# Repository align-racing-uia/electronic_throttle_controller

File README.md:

<h1 align="center"> Electronic Throttle Body Controller </h1> <br>
<p align="center">
    
</p>

<!-- START doctoc generate TOC please keep comment here to allow auto update -->
<!-- DON'T EDIT THIS SECTION, INSTEAD RE-RUN doctoc TO UPDATE -->
## Table of contents

- [Introduction](#introduction)
- [Align Racing UiA](#alignracinguia)
- [Rules for file structure](#rulesforfilestructure)
- [License](#license)

<!-- END doctoc generated TOC please keep comment here to allow auto update -->

## Introduction

This is the repository for Align Racing's formula student race car's different systems.

## Align Racing UiA

<a href="http://www.alignracing.no/">Align Racing UiA (AR)</a> is a multidisciplinary student organisation at <a href="https://www.uia.no/">The University of Agder (UiA)</a>, that take part in the world’s largest yearly engineering competition; <a href="https://www.imeche.org/events/formula-student">Formula Student (FS)</a>. The organisation continuously consists of around 60 students, from a wide variety of disciplines. The competition includes developing, building, budgeting and marketing a small scale formula type racing car. AR takes this a bit further by having more focus on developing a strong organisation, open for all disciplines, that gives the members a taste of future work-life.

## Rules

## Contribution

## License
All content included in this Git repository is under the license:

Creative Commons Attribution-NonCommercial-ShareAlike 4.0 International

You are free to:
* <b> Share </b> — copy and redistribute the material in any medium or format
* <b> Adapt </b> — remix, transform, and build upon the material

Under the following terms:
* <b> Attribution </b> — You must give appropriate credit, provide a link to the license, and indicate if changes were made. You may do so in any reasonable manner, but not in any way that suggests the licensor endorses you or your use.
* <b> NonCommercial </b> — You may not use the material for commercial purposes.
* <b> ShareAlike </b> — If you remix, transform, or build upon the material, you must distribute your contributions under the same license as the original.
* <b> No additional restrictions </b> — You may not apply legal terms or technological measures that legally restrict others from doing anything the license permits.

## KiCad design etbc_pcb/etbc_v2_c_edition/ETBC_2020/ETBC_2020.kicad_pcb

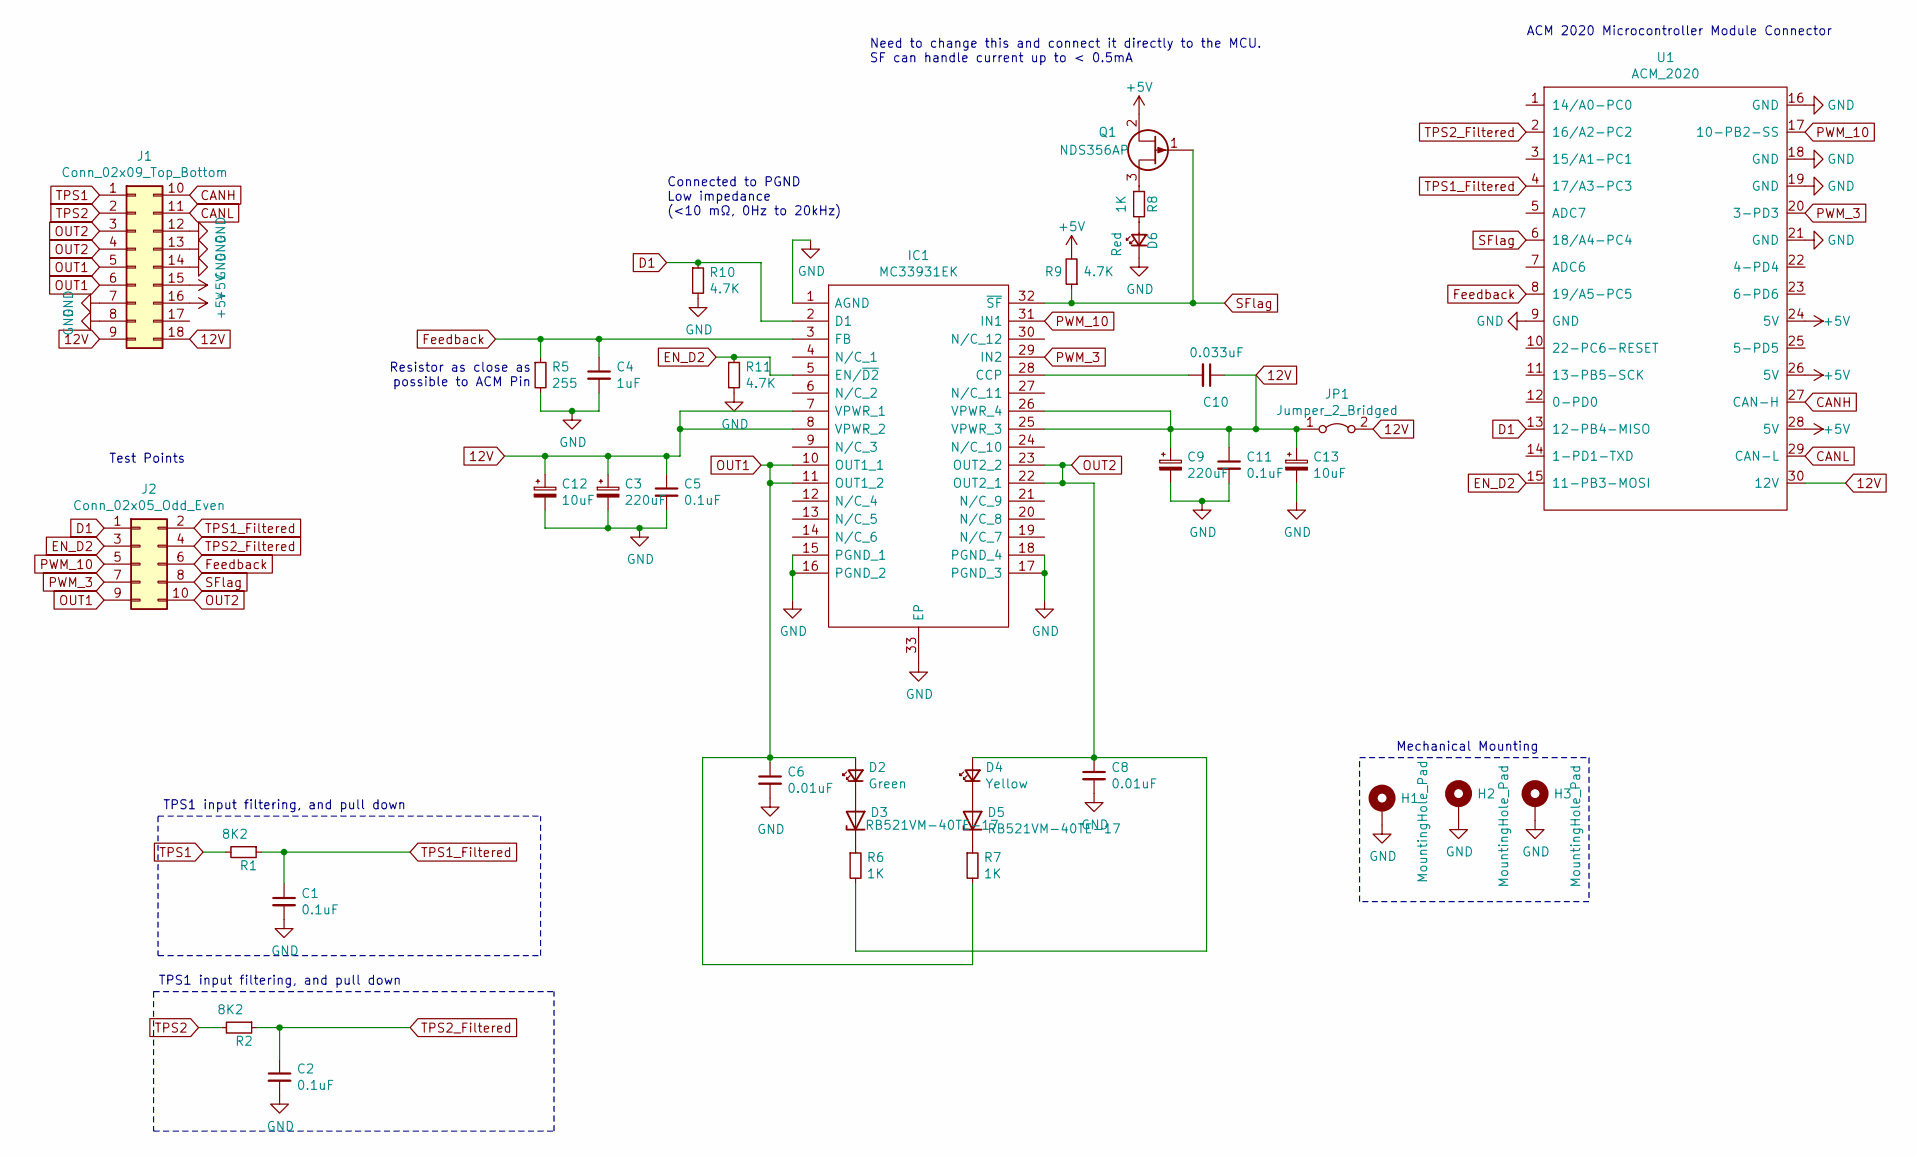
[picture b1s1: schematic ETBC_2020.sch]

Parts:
C1, C2, C5, C11: 0.1uF; C_0603_1608Metric_Pad1.05x0.95mm_HandSolder
C3, C9: 220uF; CP_Elec_6.3x7.7
C4: 1uF; C_0603_1608Metric_Pad1.05x0.95mm_HandSolder
C6, C8: 0.01uF; C_0603_1608Metric_Pad1.05x0.95mm_HandSolder
C10: 0.033uF; C_0603_1608Metric_Pad1.05x0.95mm_HandSolder
C12, C13: 10uF; CP_EIA-3216-10_Kemet-I_Pad1.58x1.35mm_HandSolder
D2: Green; D_1206_3216Metric_Pad1.42x1.75mm_HandSolder
D3, D5: RB521VM-40TE-17; D_SOD-323F
D4: Yellow; D_1206_3216Metric_Pad1.42x1.75mm_HandSolder
D6: Red; D_1206_3216Metric_Pad1.42x1.75mm_HandSolder
H1, H2, H3: MountingHole_Pad; MountingHole_3.2mm_M3_Pad_Via
IC1: MC33931EK; SOP65P1030X245-33N; Manufacturer_Part_Number MC33931EK; Mouser Part Number 841-MC33931EK
J1: Conn_02x09_Top_Bottom; JAE_MX23A18NF1
J2: Conn_02x05_Odd_Even; PinHeader_2x05_P2.54mm_Vertical
JP1: Jumper_2_Bridged; Jumper PWR 25 26
Q1: NDS356AP; SOT-23
R1, R2: 8K2; R_0603_1608Metric_Pad1.05x0.95mm_HandSolder
R5: 255; R_0603_1608Metric_Pad1.05x0.95mm_HandSolder
R6, R7, R8: 1K; R_0603_1608Metric_Pad1.05x0.95mm_HandSolder
R9, R10, R11: 4.7K; R_0603_1608Metric_Pad1.05x0.95mm_HandSolder
U1: ACM_2020; ACM_2020_Footprint_wo_silk

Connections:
12V: C3.1, C5.1, C9.1, C10.1, C11.1, C12.1, C13.1, IC1.7 (VPWR_1), IC1.8 (VPWR_2), IC1.25 (VPWR_3), IC1.26 (VPWR_4), J1.9, J1.18, JP1.1 (A), JP1.2 (B), U1.30 (12V)
+5V: J1.15, J1.16, Q1.2 (S), R9.2, U1.24 (5V), U1.26 (5V), U1.28 (5V)
CANH: J1.10, U1.27 (CAN-H)
CANL: J1.11, U1.29 (CAN-L)
D1: IC1.2 (D1), J2.1, R10.1, U1.13 (12-PB4-MISO)
EN_D2: IC1.5 (EN/~D2), J2.3, R11.1, U1.15 (11-PB3-MOSI)
Feedback: C4.1, IC1.3 (FB), J2.6, R5.1, U1.8 (19/A5-PC5)
GND: C1.2, C2.2, C3.2, C4.2, C5.2, C6.2, C8.2, C9.2, C11.2, C12.2, C13.2, D6.1 (K), H1.1, H2.1, H3.1, IC1.1 (AGND), IC1.15 (PGND_1), IC1.16 (PGND_2), IC1.17 (PGND_3), IC1.18 (PGND_4), IC1.33 (EP), J1.7, J1.8, J1.12, J1.13, J1.14, R5.2, R10.2, R11.2, U1.9 (GND), U1.16 (GND), U1.18 (GND), U1.19 (GND), U1.21 (GND)
unnamed: C10.2, IC1.28 (CCP)
unnamed: D2.1 (K), D3.2 (A)
unnamed: D3.1 (K), R6.1
unnamed: D4.1 (K), D5.2 (A)
unnamed: D5.1 (K), R7.1
unnamed: D6.2 (A), R8.2
unnamed: Q1.3 (D), R8.1
OUT1: C6.1, D2.2 (A), IC1.10 (OUT1_1), IC1.11 (OUT1_2), J1.5, J1.6, J2.9, R7.2
OUT2: C8.1, D4.2 (A), IC1.22 (OUT2_1), IC1.23 (OUT2_2), J1.3, J1.4, J2.10, R6.2
PWM_3: IC1.29 (IN2), J2.7, U1.20 (3-PD3)
PWM_10: IC1.31 (IN1), J2.5, U1.17 (10-PB2-SS)
SFlag: IC1.32 (~SF), J2.8, Q1.1 (G), R9.1, U1.6 (18/A4-PC4)
TPS1: J1.1, R1.2
TPS1_Filtered: C1.1, J2.2, R1.1, U1.4 (17/A3-PC3)
TPS2: J1.2, R2.2
TPS2_Filtered: C2.1, J2.4, R2.1, U1.2 (16/A2-PC2)

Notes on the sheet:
TPS1 input filtering, and pull down
Resistor as close as possible to ACM Pin
Connected to PGND Low impedance (<10 mΩ, 0Hz to 20kHz)
Need to change this and connect it directly to the MCU. SF can handle current up to < 0.5mA
Mechanical Mounting
Test Points
ACM 2020 Microcontroller Module Connector

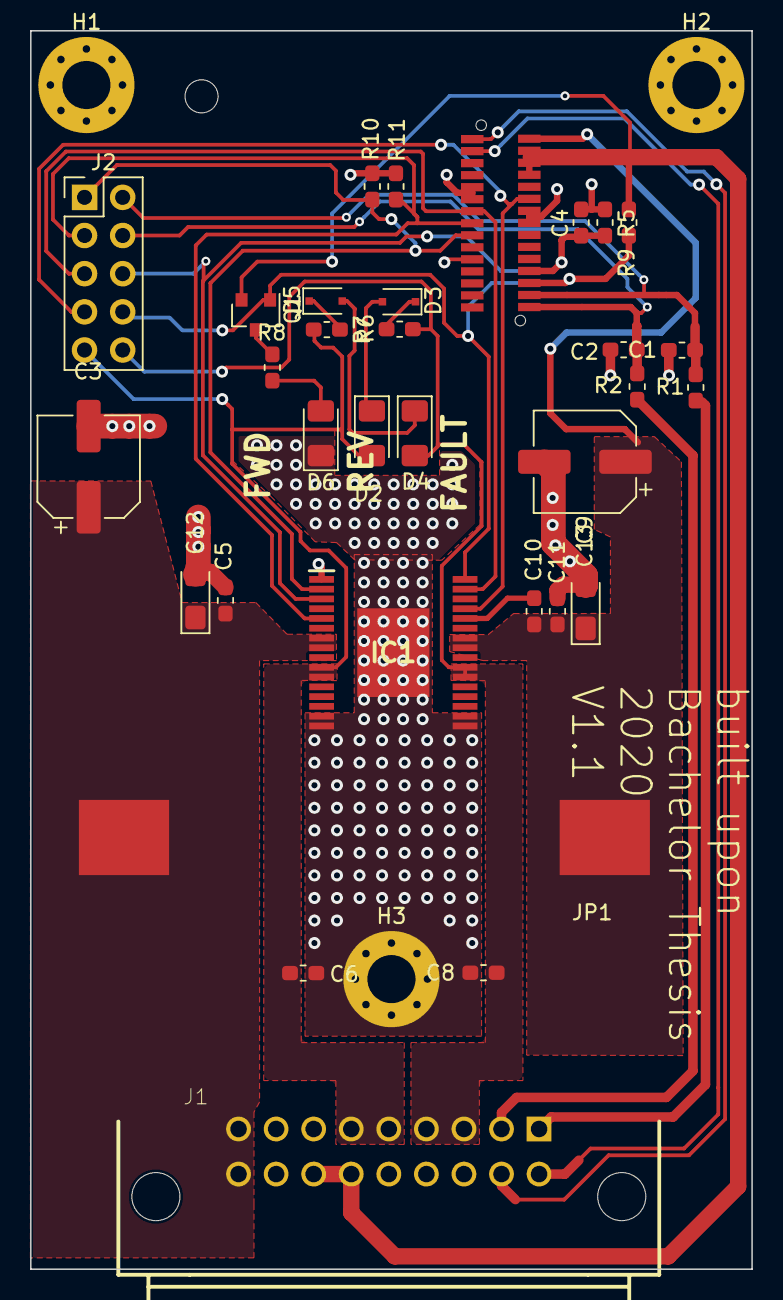
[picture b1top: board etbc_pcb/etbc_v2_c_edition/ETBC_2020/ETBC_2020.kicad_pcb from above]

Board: 2 copper layers, 48.0 x 82.4 mm, 35 parts (0 on the bottom side), 24 nets.

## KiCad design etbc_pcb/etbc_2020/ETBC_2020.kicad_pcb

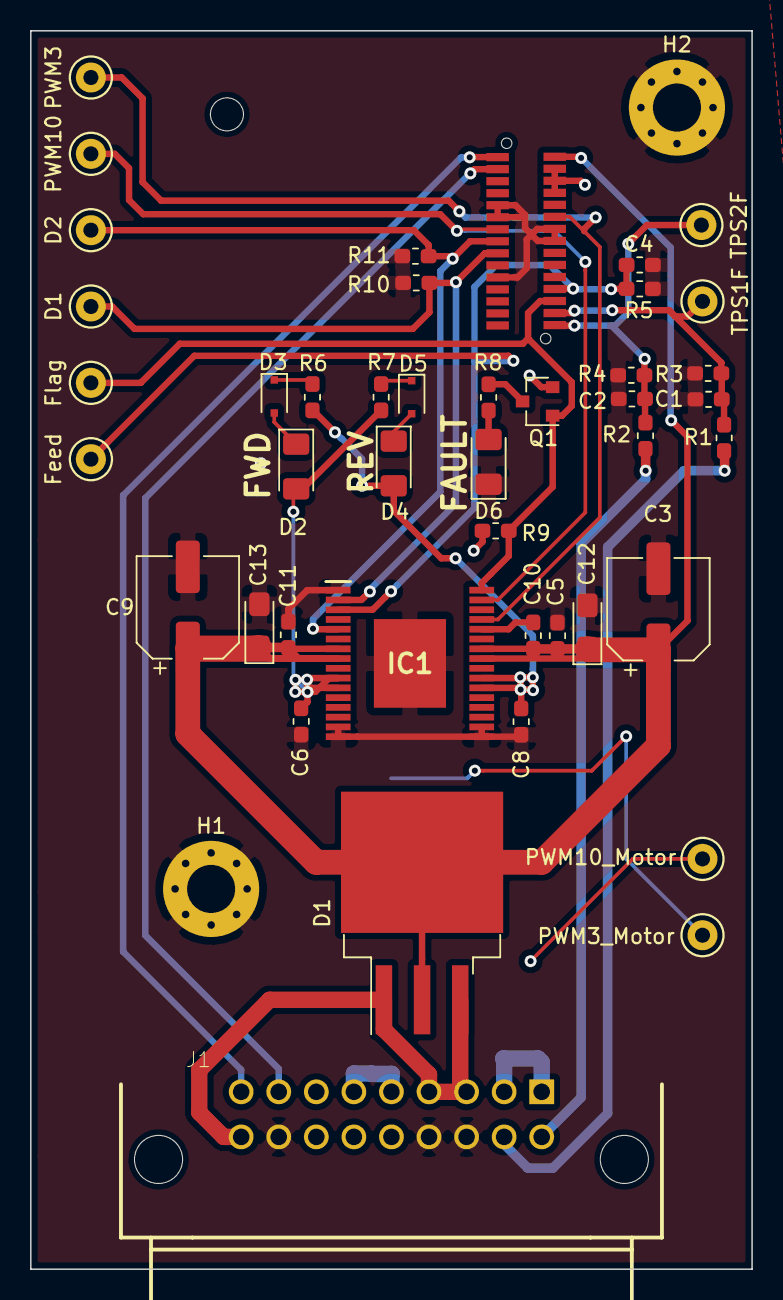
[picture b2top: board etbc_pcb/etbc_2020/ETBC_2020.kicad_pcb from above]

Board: 2 copper layers, 48.0 x 82.4 mm, 45 parts (0 on the bottom side), 25 nets.

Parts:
C1, C2, C5, C11: 0.1uF; C_0603_1608Metric_Pad1.05x0.95mm_HandSolder
C3, C9: 220uF; CP_Elec_6.3x7.7
C4: 1uF; C_0603_1608Metric_Pad1.05x0.95mm_HandSolder
C6, C8: 0.01uF; C_0603_1608Metric_Pad1.05x0.95mm_HandSolder
C10: 0.033uF; C_0603_1608Metric_Pad1.05x0.95mm_HandSolder
C12, C13: 10uF; CP_EIA-3216-10_Kemet-I_Pad1.58x1.35mm_HandSolder
D1: WNS20S100CB; TO-263-3_TabPin2
D2: Green; D_1206_3216Metric_Pad1.42x1.75mm_HandSolder
D3, D5: RB521VM-40TE-17; D_SOD-323F
D4: Yellow; D_1206_3216Metric_Pad1.42x1.75mm_HandSolder
D6: Red; D_1206_3216Metric_Pad1.42x1.75mm_HandSolder
H1, H2: MountingHole_Pad; MountingHole_3.2mm_M3_Pad_Via
IC1: MC33931EK; SOP65P1030X245-33N
J1: Conn_02x09_Top_Bottom; JAE_MX23A18NF1
Q1: NDS356AP; SOT-23
R1, R2: 8K2; R_0603_1608Metric_Pad1.05x0.95mm_HandSolder
R3, R4, R9, R10, R11: 4.7K; R_0603_1608Metric_Pad1.05x0.95mm_HandSolder
R5: 255; R_0603_1608Metric_Pad1.05x0.95mm_HandSolder
R6, R7, R8: 1K; R_0603_1608Metric_Pad1.05x0.95mm_HandSolder
TP1: PWM3; TestPoint_Keystone_5000-5004_Miniature
TP2: PWM10; TestPoint_Keystone_5000-5004_Miniature
TP3: D2; TestPoint_Keystone_5000-5004_Miniature
TP4: D1; TestPoint_Keystone_5000-5004_Miniature
TP5: Feed; TestPoint_Keystone_5000-5004_Miniature
TP6: Flag; TestPoint_Keystone_5000-5004_Miniature
TP7: TPS1F; TestPoint_Keystone_5000-5004_Miniature
TP8: TPS2F; TestPoint_Keystone_5000-5004_Miniature
TP9: PWM3_Motor; TestPoint_Keystone_5000-5004_Miniature
TP10: PWM10_Motor; TestPoint_Keystone_5000-5004_Miniature
U1: ACM_2020; ACM_2020_Footprint_wo_silk

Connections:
12V: D1.1, D1.3, J1.3, J1.4, J1.18
+5V: J1.15, J1.16, Q1.2, R9.2, U1.24, U1.26, U1.28
CANH: J1.8, U1.27
CANL: J1.9, U1.29
D1: IC1.2, R10.1, TP4.1, U1.13
EN_D2: IC1.5, R11.1, TP3.1, U1.15
Feedback: C4.1, IC1.3, R5.1, TP5.1, U1.8
GND: C1.2, C2.2, C3.2, C4.2, C5.2, C6.2, C8.2, C9.2, C11.2, C12.2, C13.2, D6.1, H1.1, H2.1, IC1.1, IC1.15, IC1.16, IC1.17, IC1.18, IC1.33, J1.12, J1.13, J1.17, R3.2, R4.2, R5.2, R10.2, R11.2, U1.9, U1.16, U1.18, U1.19, U1.21
unnamed: C10.2, IC1.28
unnamed: D2.1, D3.2
unnamed: D3.1, R6.1
unnamed: D4.1, D5.2
unnamed: D5.1, R7.1
unnamed: D6.2, R8.2
unnamed: Q1.3, R8.1
OUT1: C6.1, D2.2, IC1.10, IC1.11, J1.5, J1.6, R7.2, TP9.1
OUT2: C8.1, D4.2, IC1.22, IC1.23, J1.1, J1.2, R6.2, TP10.1
PWM_3: IC1.29, TP1.1, U1.20
PWM_10: IC1.31, TP2.1, U1.17
PWR: C3.1, C5.1, C9.1, C10.1, C11.1, C12.1, C13.1, D1.2, IC1.7, IC1.8, IC1.25, IC1.26, U1.30
SFlag: IC1.32, Q1.1, R9.1, TP6.1, U1.6
TPS1: J1.11, R1.2
TPS1_Filtered: C1.1, R1.1, R3.1, TP7.1, U1.4
TPS2: J1.10, R2.2
TPS2_Filtered: C2.1, R2.1, R4.1, TP8.1, U1.2

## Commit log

2021-08-01 Directory refactoring.
